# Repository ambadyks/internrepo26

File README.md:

# internrepo26

internship 2026 ----:)

------

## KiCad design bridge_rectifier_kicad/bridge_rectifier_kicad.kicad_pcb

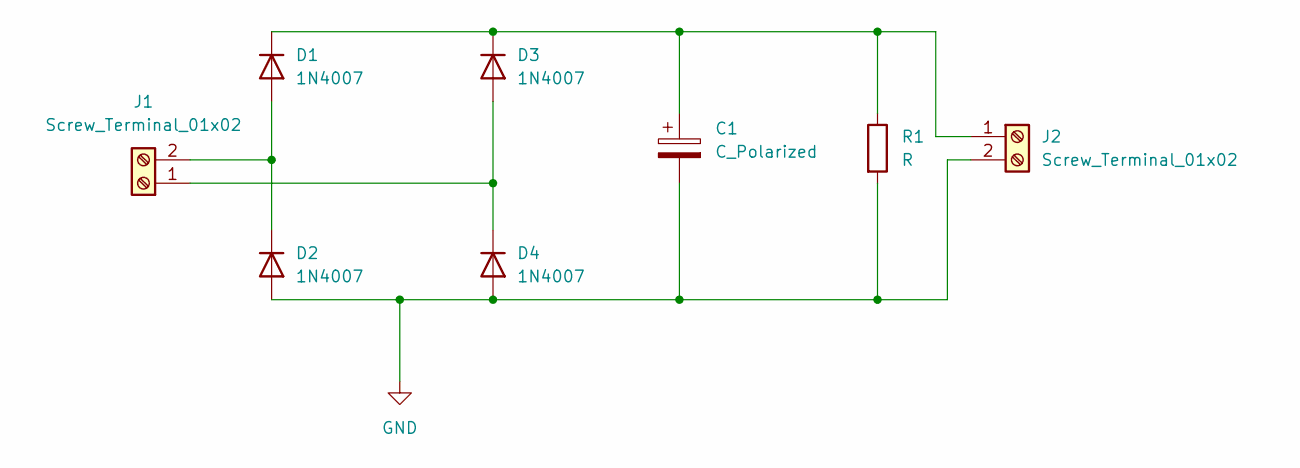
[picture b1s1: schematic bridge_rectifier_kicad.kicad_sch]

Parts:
C1: C_Polarized; CP_Radial_D10.0mm_P5.00mm
D1, D2, D3, D4: 1N4007; D_DO-41_SOD81_P10.16mm_Horizontal
J1, J2: Screw_Terminal_01x02; TerminalBlock_MaiXu_MX126-5.0-02P_1x02_P5.00mm
R1: R; R_Axial_DIN0309_L9.0mm_D3.2mm_P12.70mm_Horizontal

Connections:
GND: C1.2, D2.2 (A), D4.2 (A), J2.2, R1.2
unnamed: D1.2 (A), D2.1 (K), J1.2
unnamed: C1.1, D1.1 (K), D3.1 (K), J2.1, R1.1
unnamed: D3.2 (A), D4.1 (K), J1.1

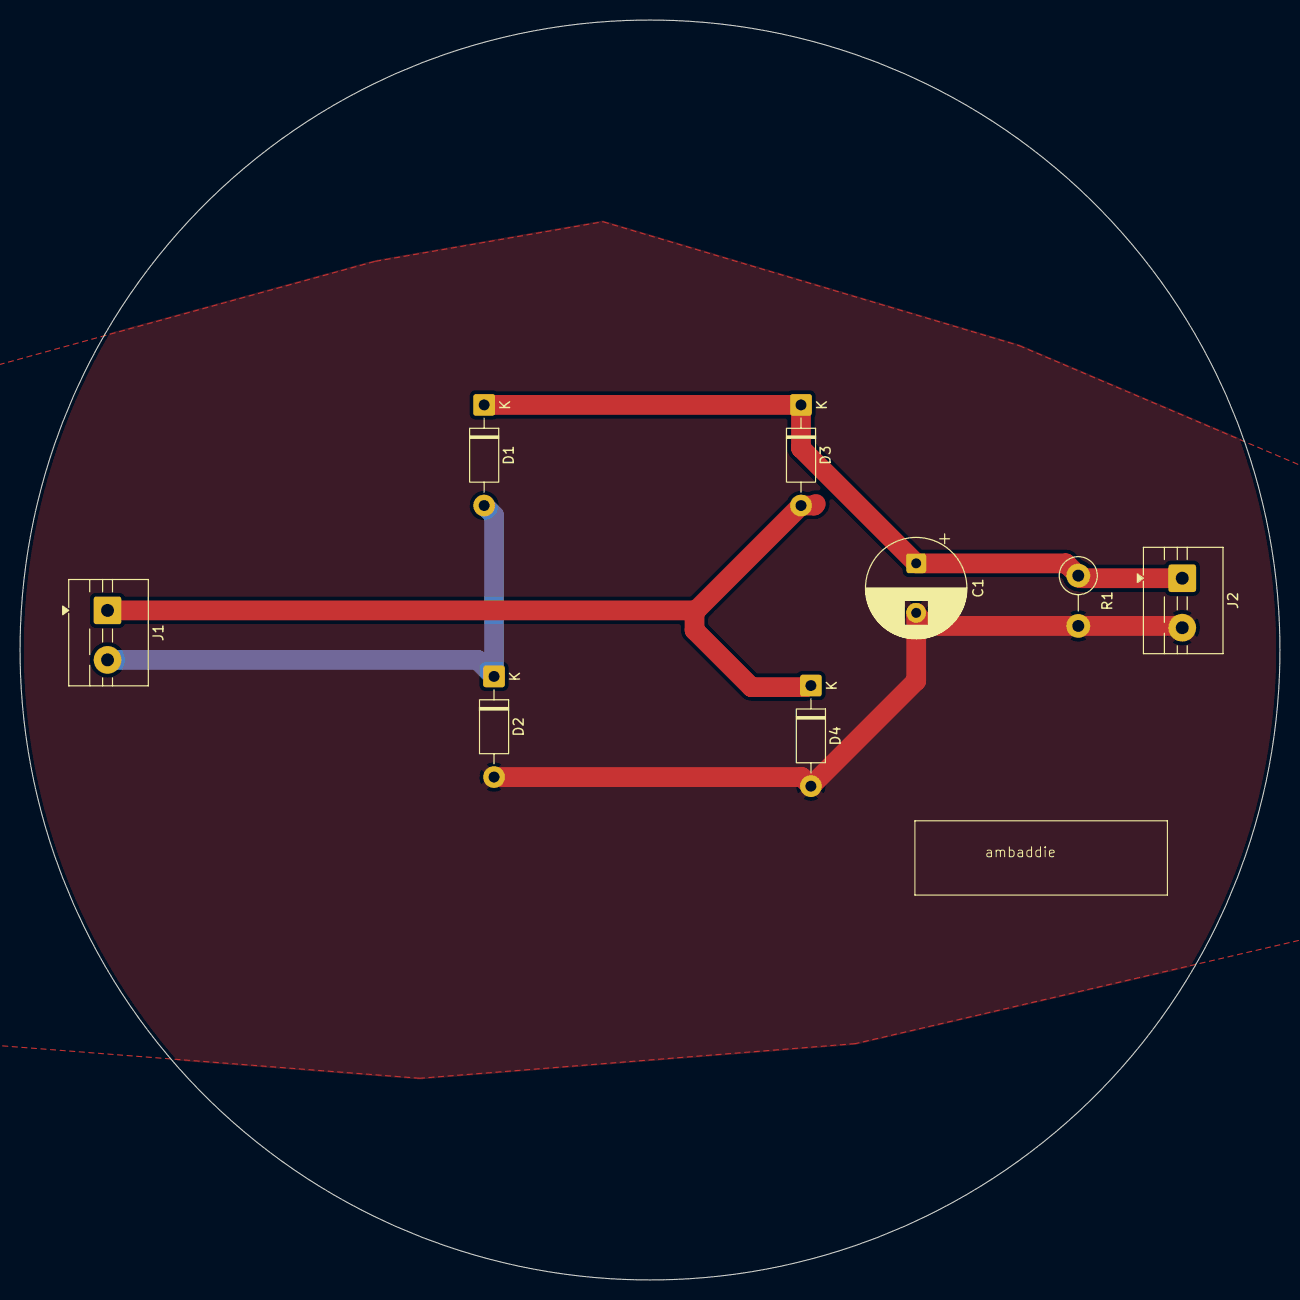
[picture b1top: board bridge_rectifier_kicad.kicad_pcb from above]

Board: 2 copper layers, 127.2 x 127.2 mm, 8 parts (0 on the bottom side), 4 nets.

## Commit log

2026-06-19 Add portfolio website and Firebase hosting
2026-06-19 Add entryPoint to Firebase hosting workflow
2026-06-19 Fix public directory name
2026-06-19 Added darkmode
2026-06-19 dark mode feature add
2026-06-20 fixed name appearing twice
2026-06-25 Added Firebase website and ESP32 control
2026-06-25 Fix Firebase Hosting workflow
2026-06-25 improved website functionality
2026-06-29 Add MotionSense AI project and bridge rectifier KiCad design
2026-06-29 Fix Firebase action entry point
2026-06-29 Trigger Firebase deployment
2026-06-29 Remove Firebase preview workflow
2026-06-29 Use Firebase CLI for deployment
